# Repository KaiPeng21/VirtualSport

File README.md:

# VirtualSport
ECE477 Digital System Design Project

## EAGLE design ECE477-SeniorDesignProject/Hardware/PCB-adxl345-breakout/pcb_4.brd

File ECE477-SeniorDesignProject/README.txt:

Virtual Sport Project

ECE 477 Team 3
Fall 2017

Chia-Hua Peng
Hengyi Lin
Lingke Yu
Yutao Hu

Video: https://youtu.be/kOvK4SmzFe8

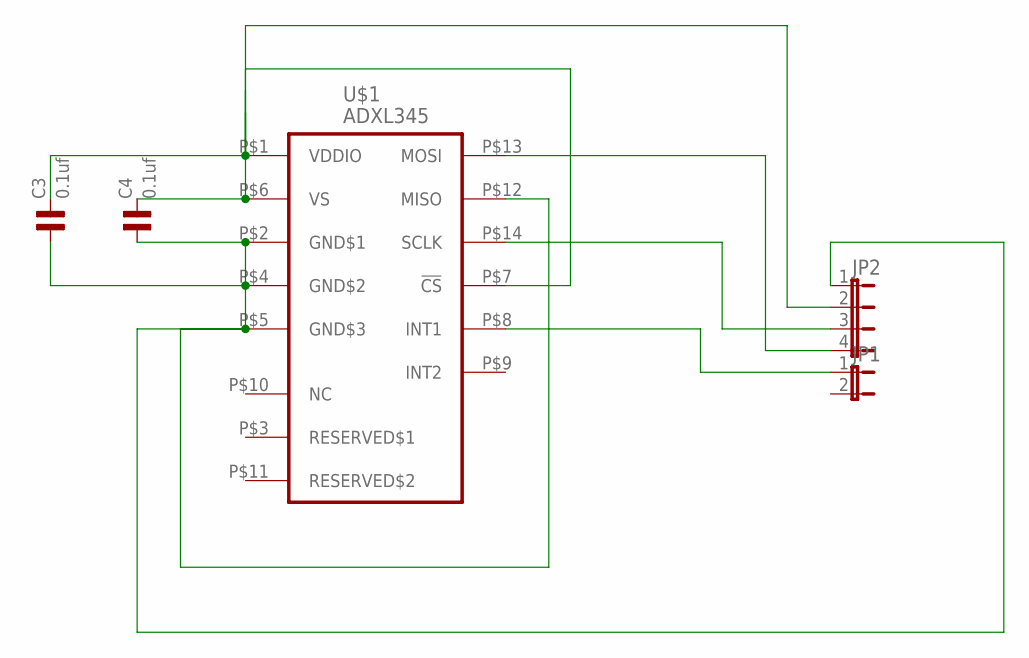
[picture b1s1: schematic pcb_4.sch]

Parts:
C3, C4: 0.1uf; 0805
JP1: JP1E; JP1
JP2: JP4E; JP4
U$1: ADXL345; LGA14

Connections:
unnamed: C3.1, C4.1, JP2.1, U$1.P$2 (GND$1), U$1.P$4 (GND$2), U$1.P$5 (GND$3), U$1.P$12 (MISO)
unnamed: C3.2, C4.2, JP2.2, U$1.P$1 (VDDIO), U$1.P$6 (VS), U$1.P$7 (!CS)
unnamed: JP2.4, U$1.P$13 (MOSI)
unnamed: JP2.3, U$1.P$14 (SCLK)
unnamed: JP1.1, U$1.P$8 (INT1)

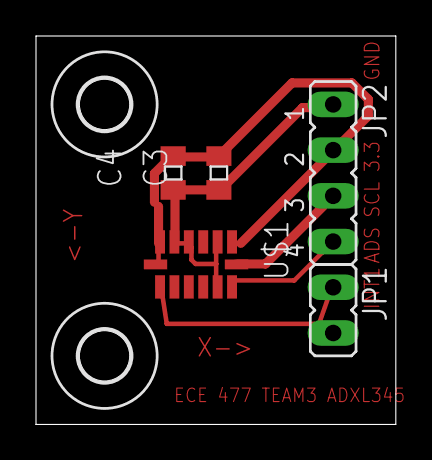
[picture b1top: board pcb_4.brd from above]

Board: 2 copper layers, 20.0 x 21.6 mm, 7 parts (0 on the bottom side), 5 nets.

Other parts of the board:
U$2, U$3: 2,8

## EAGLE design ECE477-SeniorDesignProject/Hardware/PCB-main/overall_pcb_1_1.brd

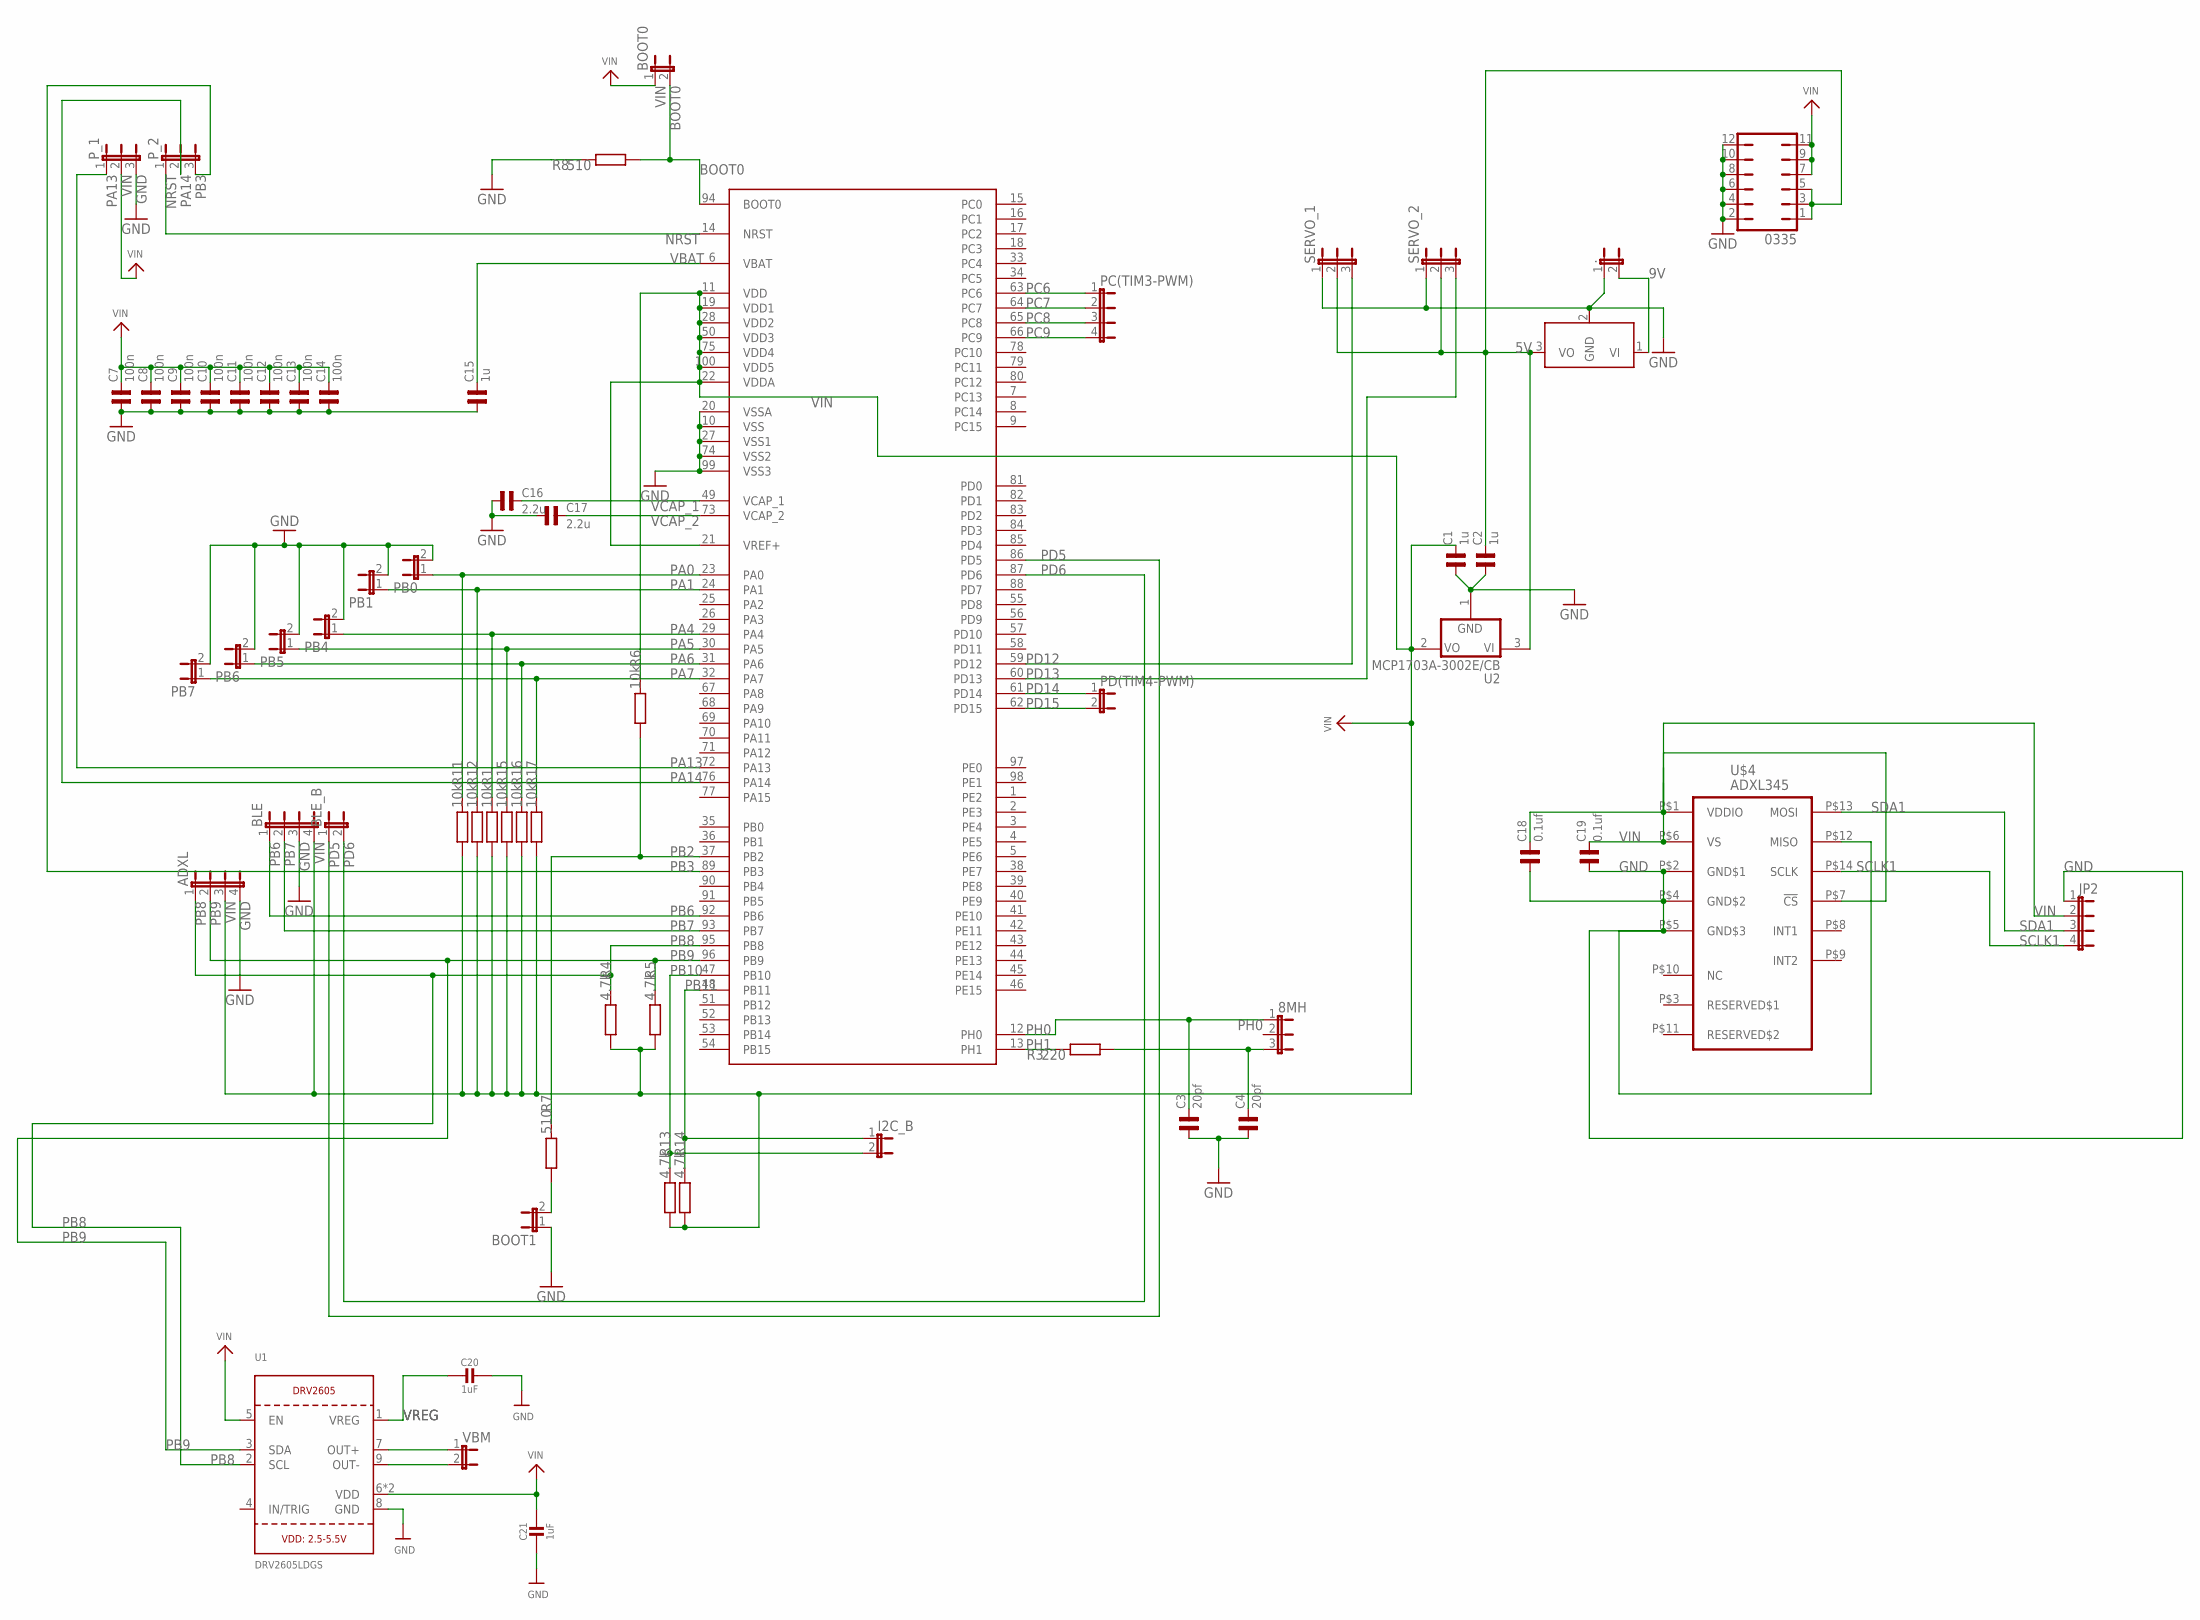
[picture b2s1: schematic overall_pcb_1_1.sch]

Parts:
8MH: JP2E; JP2
0335: JP6Q
.: JP1E; JP1
ADXL: JP4E; JP4
BLE: JP4E; JP4
BLE_B: JP1E; JP1
BOOT0, BOOT1: JP1E; JP1
C1, C2, C15: 1u; 0805
C3, C4: 20pf; 0805
C7, C8, C9, C10, C11, C12, C13, C14: 100n; 0805
C16, C17: 2.2u; 0805
C18, C19: 0.1uf; 0805
C20, C21: 1uF; 0805-NO
I2C_B: JP1E; JP1
JP2: JP4E; JP4
PB0, PB1, PB4, PB5, PB6, PB7: JP1E; JP1
PC(TIM3-PWM): JP4E; JP4
PD(TIM4-PWM): JP1E; JP1
P_1, P_2: JP2E; JP2
R1, R6, R11, R12, R15, R16, R17: 10k; R0805
R3: 220; R0805
R4, R5, R13, R14: 4.7k; R0805
R7, R8: 510; R0805
SERVO_1, SERVO_2: JP2E; JP2
U1: DRV2605LDGS; PSOP10
U2: MCP1703A-3002E/CB; SOT23A_MICROCHIP_CB
U$1: STM32F40XSTM32D40X; LQFP100
U$2: DCDC_OKI-78SR; OKI-78SRH
U$4: ADXL345; LGA14
VBM: JP1E; JP1

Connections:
5V: 0335.1, 0335.3, 0335.5, C2.2, SERVO_1.2, SERVO_2.2, U2.3 (VI), U$2.3 (VO)
9V: ..2, U$2.1 (VI)
BOOT0: BOOT0.2, R8.1, U$1.94 (BOOT0)
GND: 0335.2, 0335.4, 0335.6, 0335.8, 0335.10, 0335.12, ..1, ADXL.4, BLE.3, BOOT1.1, C1.1, C2.1, C3.1, C4.1, C7.1, C8.1, C9.1, C10.1, C11.1, C12.1, C13.1, C14.1, C15.1, C16.1, C17.1, C18.1, C19.1, C20.1, C21.2, JP2.1, PB0.2, PB1.2, PB4.2, PB5.2, PB6.2, PB7.2, P_1.3, R8.2, SERVO_1.1, SERVO_2.1, U1.8 (GND), U2.1 (GND), U$1.10 (VSS), U$1.20 (VSSA), U$1.27 (VSS1), U$1.74 (VSS2), U$1.99 (VSS3), U$2.2 (GND), U$4.P$2 (GND$1), U$4.P$4 (GND$2), U$4.P$5 (GND$3), U$4.P$12 (MISO)
unnamed: BOOT1.2, R7.1
unnamed: 8MH.3, C4.2, R3.1
NRST: P_2.1, U$1.14 (NRST)
OUT+: U1.7 (OUT+), VBM.1
OUT-: U1.9 (OUT-), VBM.2
PA0: PB0.1, R11.2, U$1.23 (PA0)
PA1: PB1.1, R12.2, U$1.24 (PA1)
PA4: PB4.1, R1.2, U$1.29 (PA4)
PA5: PB5.1, R15.2, U$1.30 (PA5)
PA6: PB6.1, R16.2, U$1.31 (PA6)
PA7: PB7.1, R17.2, U$1.32 (PA7)
PA13: P_1.1, U$1.72 (PA13)
PA14: P_2.2, U$1.76 (PA14)
PB2: R6.1, R7.2, U$1.37 (PB2)
PB3: P_2.3, U$1.89 (PB3)
PB6: BLE.1, U$1.92 (PB6)
PB7: BLE.2, U$1.93 (PB7)
PB8: ADXL.1, R4.2, U1.2 (SCL), U$1.95 (PB8)
PB9: ADXL.2, R5.2, U1.3 (SDA), U$1.96 (PB9)
PB10: I2C_B.2, R13.2, U$1.47 (PB10)
PB11: I2C_B.1, R14.2, U$1.48 (PB11)
PC6: PC(TIM3-PWM).1, U$1.63 (PC6)
PC7: PC(TIM3-PWM).2, U$1.64 (PC7)
PC8: PC(TIM3-PWM).3, U$1.65 (PC8)
PC9: PC(TIM3-PWM).4, U$1.66 (PC9)
PD5: BLE_B.1, U$1.86 (PD5)
PD6: BLE_B.2, U$1.87 (PD6)
PD12: SERVO_1.3, U$1.59 (PD12)
PD13: SERVO_2.3, U$1.60 (PD13)
PD14: PD(TIM4-PWM).1, U$1.61 (PD14)
PD15: PD(TIM4-PWM).2, U$1.62 (PD15)
PH0: 8MH.1, C3.2, U$1.12 (PH0)
PH1: R3.2, U$1.13 (PH1)
SCLK1: JP2.4, U$4.P$14 (SCLK)
SDA1: JP2.3, U$4.P$13 (MOSI)
VBAT: C15.2, U$1.6 (VBAT)
VCAP_1: C16.2, U$1.49 (VCAP_1)
VCAP_2: C17.2, U$1.73 (VCAP_2)
VIN: 0335.7, 0335.9, 0335.11, ADXL.3, BLE.4, BOOT0.1, C1.2, C7.2, C8.2, C9.2, C10.2, C11.2, C12.2, C13.2, C14.2, C18.2, C19.2, C21.1, JP2.2, P_1.2, R1.1, R4.1, R5.1, R6.2, R11.1, R12.1, R13.1, R14.1, R15.1, R16.1, R17.1, U1.5 (EN), U1.6 (VDD), U1.10 (VDD), U2.2 (VO), U$1.11 (VDD), U$1.19 (VDD1), U$1.21 (VREF+), U$1.22 (VDDA), U$1.28 (VDD2), U$1.50 (VDD3), U$1.75 (VDD4), U$1.100 (VDD5), U$4.P$1 (VDDIO), U$4.P$6 (VS), U$4.P$7 (!CS)
VREG: C20.2, U1.1 (VREG)

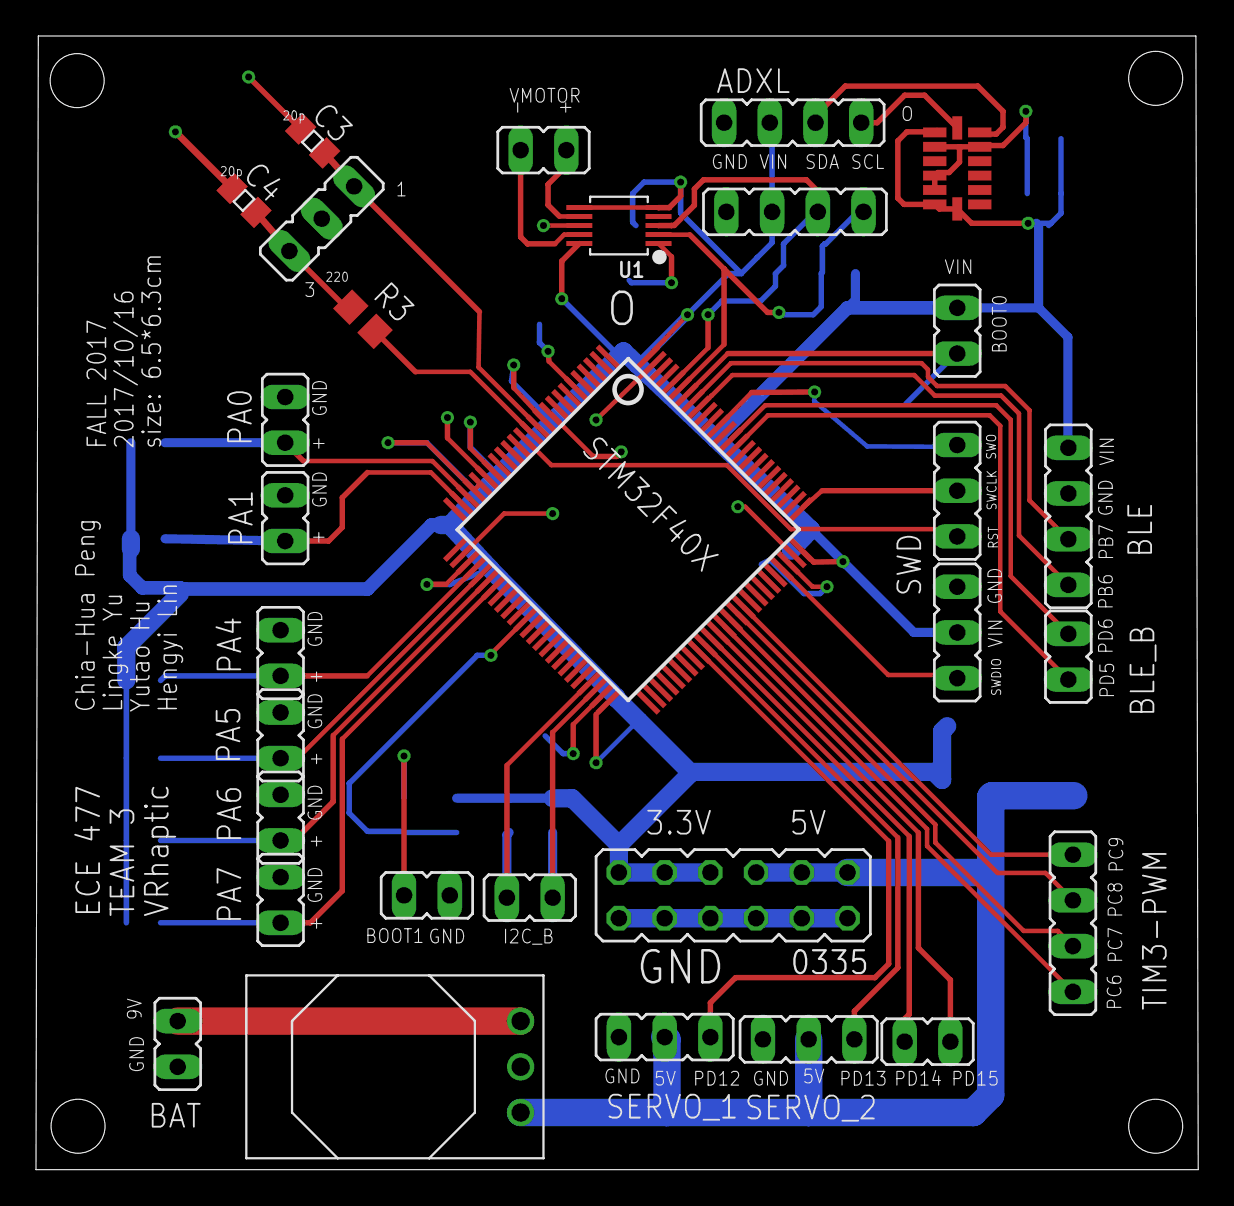
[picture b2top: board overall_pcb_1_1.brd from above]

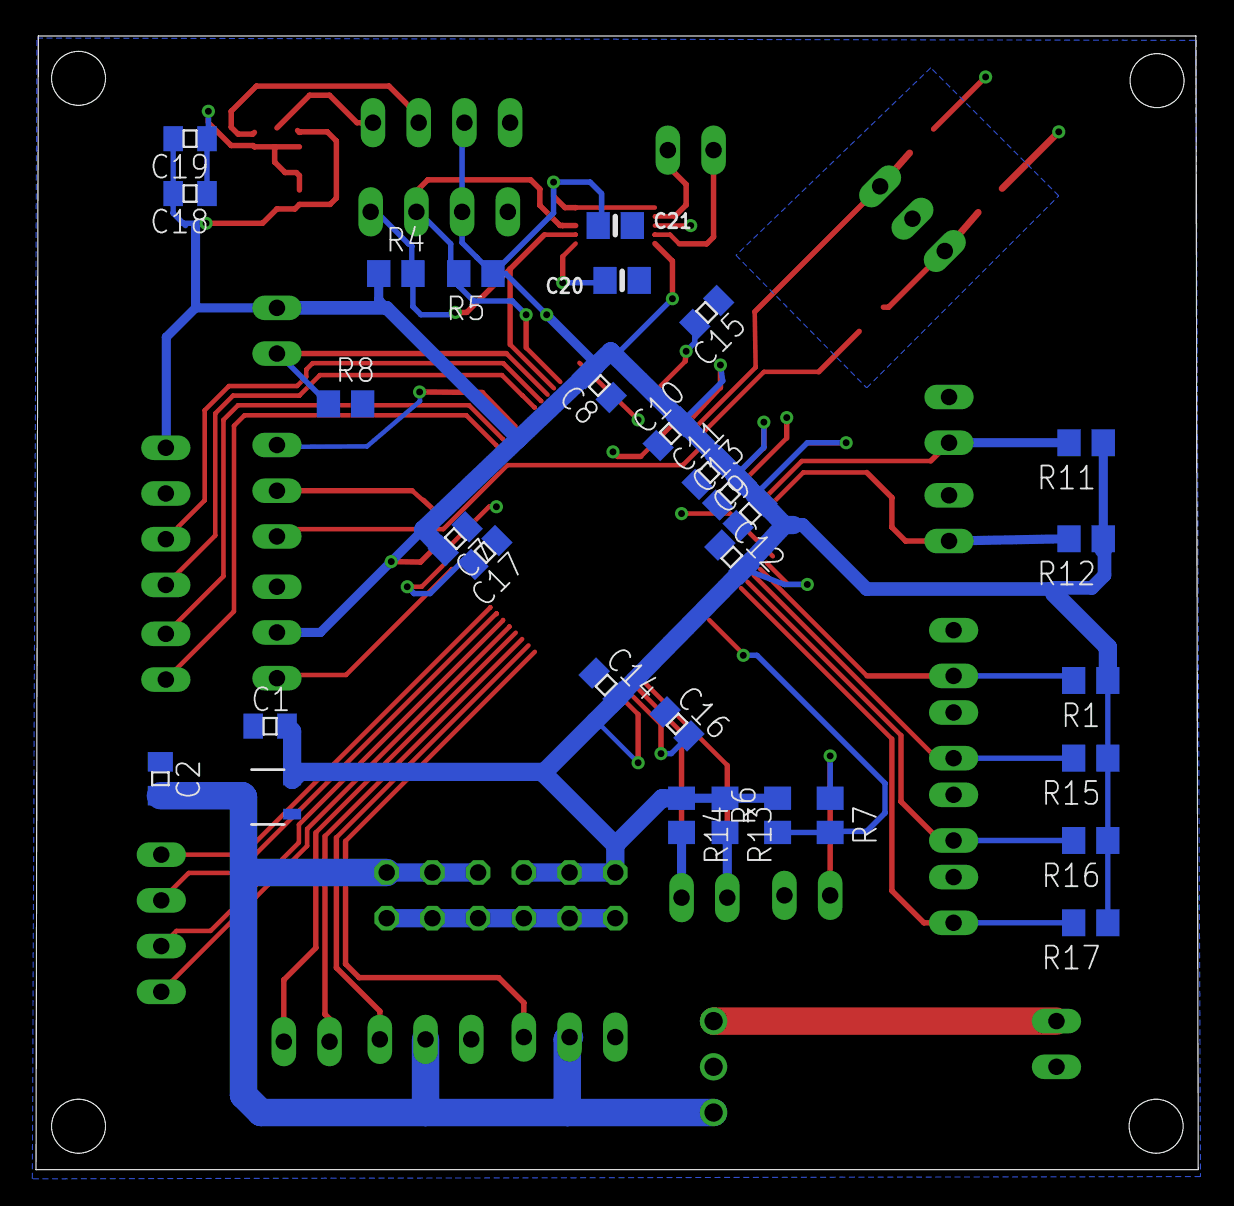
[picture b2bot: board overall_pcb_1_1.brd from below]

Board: 2 copper layers, 64.6 x 63.0 mm, 61 parts (31 on the bottom side), 44 nets.

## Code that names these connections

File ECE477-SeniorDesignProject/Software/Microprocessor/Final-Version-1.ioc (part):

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Mcu.Name=STM32F407V(E-G)Tx
Mcu.Package=LQFP100
Mcu.UserName=STM32F407VGTx
PA0-WKUP.Signal=GPIO_Input
PA1.Signal=GPIO_Input
PA13.Mode=Trace_Asynchronous_SW
PA13.Signal=SYS_JTMS-SWDIO
PA14.Mode=Trace_Asynchronous_SW
PA14.Signal=SYS_JTCK-SWCLK
PA4.Signal=GPIO_Input
PA5.Signal=GPIO_Input
PA6.Signal=GPIO_Input
PA7.Signal=GPIO_Input
PB10.Mode=I2C
PB10.Signal=I2C2_SCL
PB11.Mode=I2C
PB11.Signal=I2C2_SDA
PB3.Mode=Trace_Asynchronous_SW
PB3.Signal=SYS_JTDO-SWO
PB6.Mode=Asynchronous
PB6.Signal=USART1_TX
PB7.Mode=Asynchronous
PB7.Signal=USART1_RX
PB8.Mode=I2C
PB8.Signal=I2C1_SCL
PB9.Mode=I2C
PB9.Signal=I2C1_SDA
PC6.Signal=S_TIM3_CH1
PC7.Signal=S_TIM3_CH2
PC8.Signal=S_TIM3_CH3
PC9.Signal=S_TIM3_CH4
PD12.Signal=S_TIM4_CH1
PD13.Signal=S_TIM4_CH2
PD14.Signal=S_TIM4_CH3
PD15.Signal=S_TIM4_CH4
PD5.Mode=Asynchronous
PD5.Signal=USART2_TX
PD6.Mode=Asynchronous
PD6.Signal=USART2_RX
PH0-OSC_IN.Signal=RCC_OSC_IN
PH1-OSC_OUT.Signal=RCC_OSC_OUT
RCC.HSE_VALUE=25000000
RCC.SYSCLKFreq_VALUE=16000000
board=Final-Version-1

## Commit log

2017-12-07 documents added
2017-12-07 Mechanical added
2017-12-07 Hardware added
2017-12-07 embedded software added
2017-12-07 video link added
2017-12-07 vr scripts added

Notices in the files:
parts and their libraries:
microbuilder: This work is placed in the public domain, and may be freely used for commercial and non-commercial work with the following conditions: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
